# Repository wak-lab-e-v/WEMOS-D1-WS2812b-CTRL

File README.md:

# WEMOS D1 (ESP8266) LED Controller

Controller for WS2812B LED Strips / Panels / i.e. , optimized for the https://github.com/Aircoookie/WLED projekt

*Targets:*

- compact in a 3D printed case
- DC via hollow plug and 2A Step Down converter
- alternately over JST 3-pin (INPUT, 5V, data ignored)
- WEMOS D1 as controller
- diode protection for WEMOS D1 5V input
- Stabi-Elco in the 5V branch 
- Level Shift via 74HCT1G08GW
- Push button direct to controler (typically used as on/off via software)
- Infrarot support for IR-Remote
- PCB with Wemos-D1 und Step Down converter side-by-side

*LED Strip:*

- WS2812B-compatible RGB(W) led strip to GPIO2 / D2
- optional support for GPIO16 / D0 via solder bridge 
- level-shift via 74HCT1G08GW
- output via solder pads, JST 3-pin

*Push button:*

- a push button is connected to GPIO0 / D3

*Infrared:*

- recommended: TSOP38238
- Pinout: 2.5 V to 5.5 V, GND, Signal
- Signal to GPIO4 / D2 (can be changed in NpbWrapper.h)

*PCB:*

- D2 to Infrared solder pad
- D3 to button solder pad
- D4 to solder bridge/switch, level shifter, led signal solder pad
- D0 to solder bridge/switch, level shifter, led signal solder pad

*Wemos D1 Pinout:*

- A0	Analoger Eingang, max 3,3V	A0
- D0	IO	GPIO16
- D1	IO	GPIO5, SCL
- D2	IO	GPIO4, SDA
- D3	IO	GPIO0, 10k Pull-up
- D4	IO	GPIO2, 10k Pull-up, Onboard LED
- D5	IO  GPIO14, SCK	
- D6	IO	GPIO12, MISO
- D7	IO	GPIO13, MOSI
- D8	IO	GPIO15, 10k Pull-down, SS (Slave Select)
- GND
- 5V	(unprotected)
- 3V3	3,3V (from onboard step-down)

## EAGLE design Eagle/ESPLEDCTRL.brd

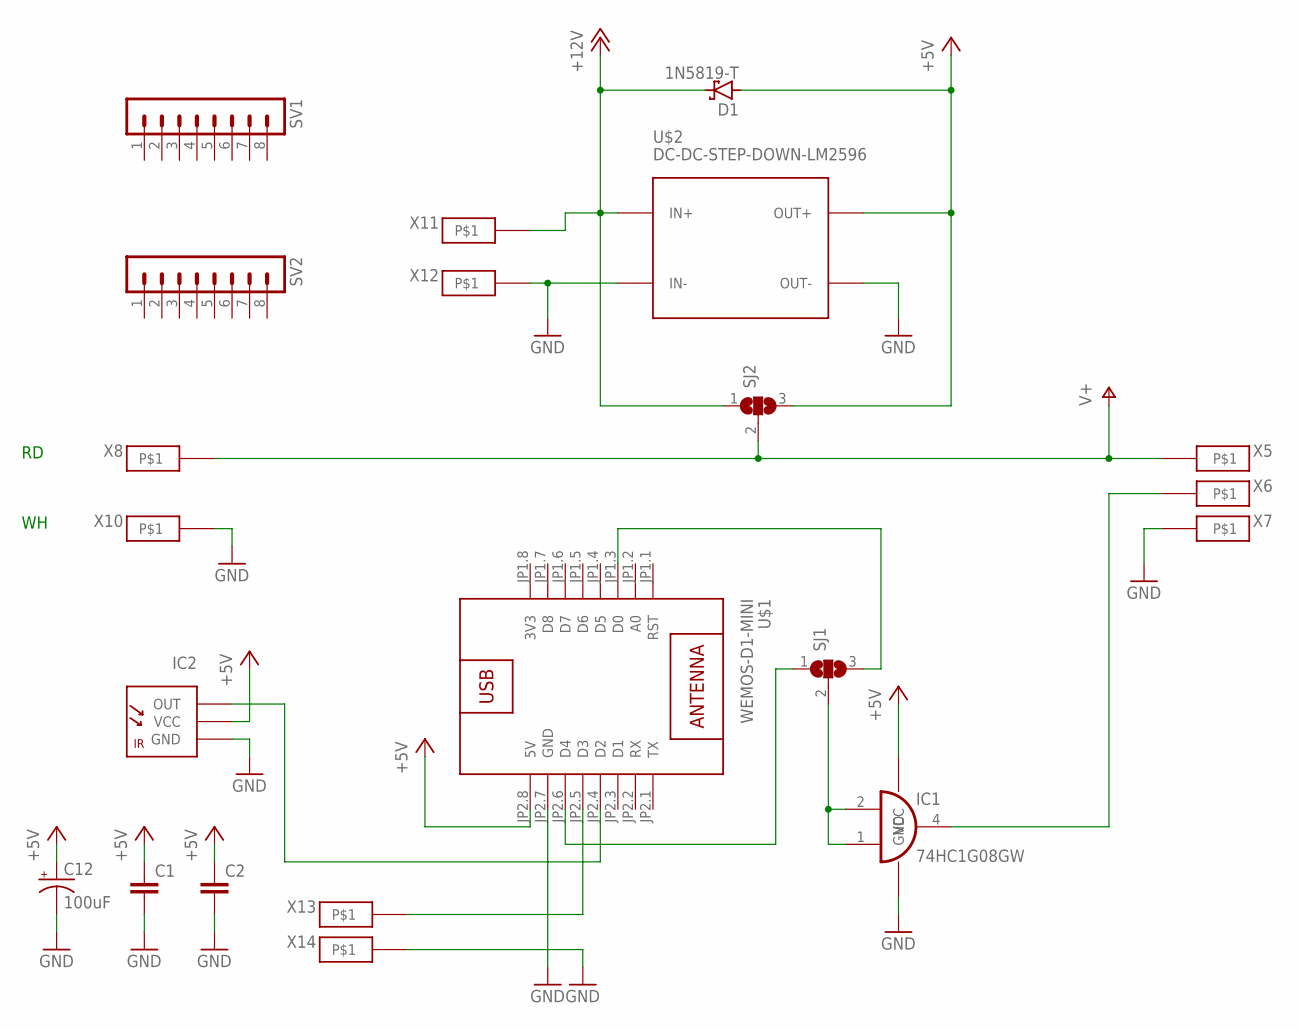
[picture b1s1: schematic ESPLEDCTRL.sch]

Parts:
C1, C2: C-EUC1206; C1206
C12: 100uF; PANASONIC_D
D1: 1N5819-T; DO41-7.6
IC1: 74HC1G08GW; SOT353
IC2: TSOP382; TSOP38
SJ1, SJ2: SJ2W; SJ_2
SV1, SV2: MA08-1
U$1: WEMOS-D1-MINI
U$2: DC-DC-STEP-DOWN-LM2596
X5, X6, X7, X8, X10, X11, X12, X13, X14: PAD2X4

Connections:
3V3: U$1.JP1.8 (3V3)
+5V: C1.1, C2.1, C12.+, D1.A, IC1.5 (VCC), IC2.3 (VCC), SJ2.3, U$1.JP2.8 (5V), U$2.OUT+
+12V: D1.C, SJ2.1, U$2.IN+, X11.P$1
GND: C1.2, C2.2, C12.-, IC1.3 (GND), IC2.2 (GND), U$1.JP2.7 (GND), U$2.IN-, U$2.OUT-, X7.P$1, X10.P$1, X12.P$1, X14.P$1
unnamed: U$1.JP2.5 (D3), X13.P$1
unnamed: IC2.1 (OUT), U$1.JP2.4 (D2)
unnamed: SJ1.1, U$1.JP2.6 (D4)
unnamed: IC1.1 (I1), IC1.2 (I0), SJ1.2
unnamed: SJ1.3, U$1.JP1.3 (D0)
unnamed: IC1.4 (O), X6.P$1
V+: SJ2.2, X5.P$1, X8.P$1

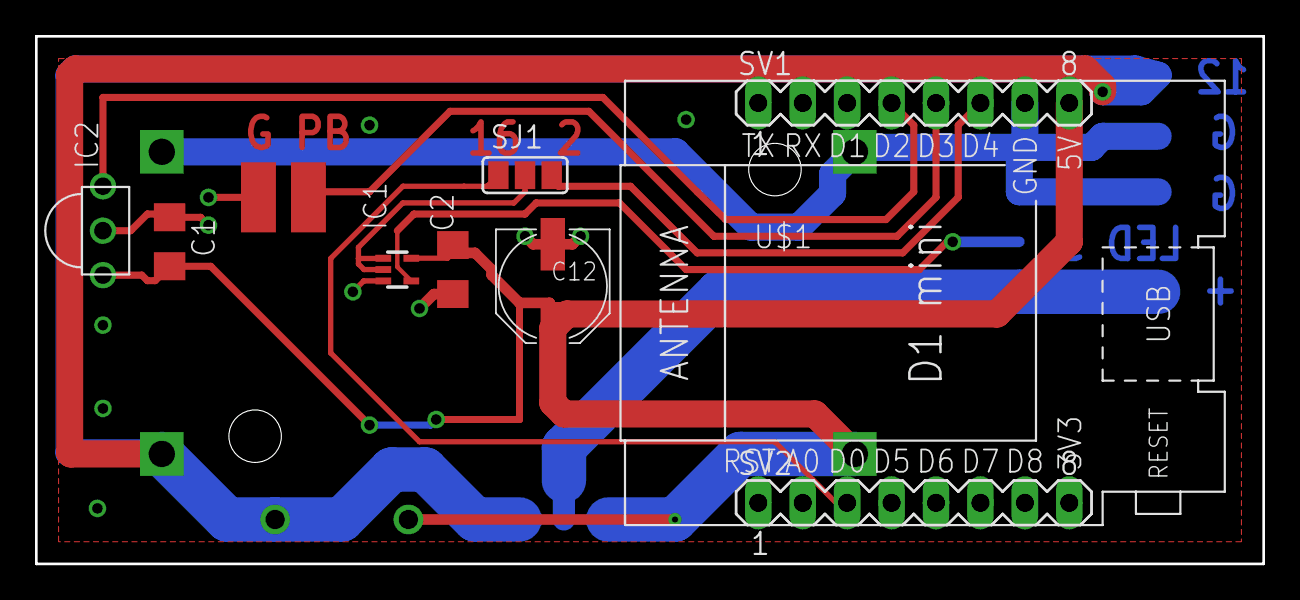
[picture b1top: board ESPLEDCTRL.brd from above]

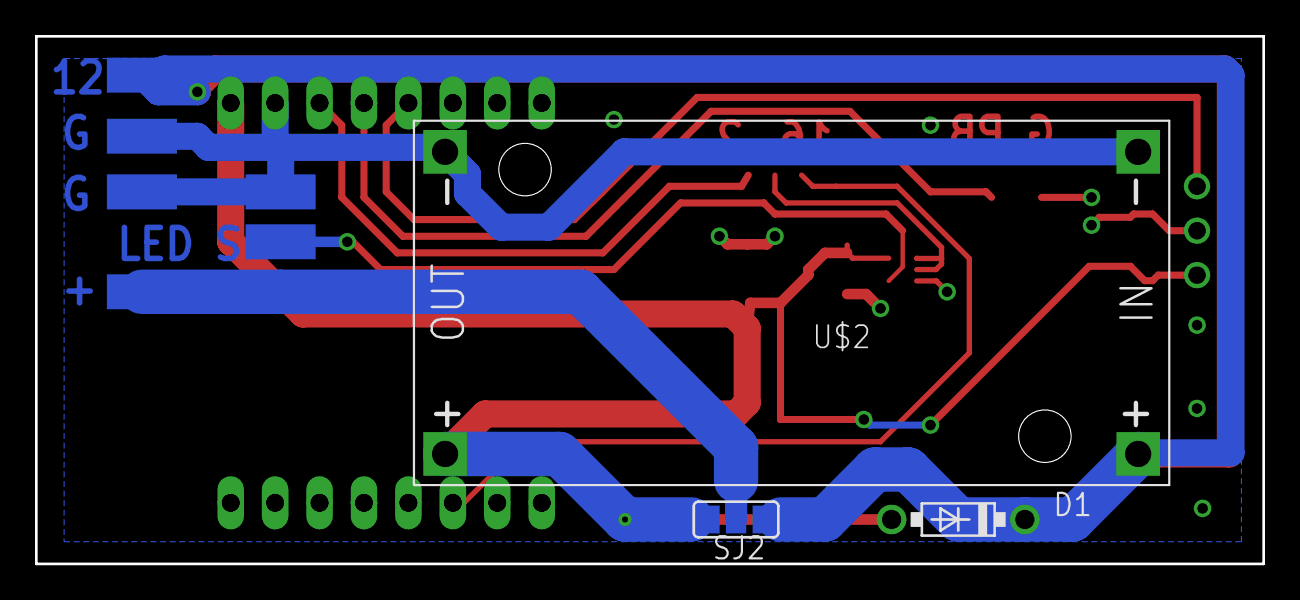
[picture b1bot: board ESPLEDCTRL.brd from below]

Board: 2 copper layers, 70.2 x 30.2 mm, 21 parts (10 on the bottom side), 10 nets.

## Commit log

2019-11-11 Initialversion
2019-11-11 Eine Diode
2019-11-11 Die Diode
2019-11-11 README.md
2019-11-13 some changes
2019-11-13 Fritzing Files added
2019-11-13 minimal changes
2020-05-03 Alte Version
2020-05-03 Umbau auf Version 2 beginnt
2020-06-21 Datasheet
2020-06-22 Leiterplatte Anordnung vorbereitet DCDC wandler ist 14mm hoch
2020-06-22 Schaltplan
2020-06-24 Board fertig gestellt
2022-06-07 Schaltplan.png aktualisiert, D1 eingefügt
2022-06-21 Umsortiert
2022-06-21 Bild
2023-04-06 Pacages
2023-04-07 LM2596

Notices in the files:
parts and their libraries:
diy-modules: Released under the Creative Commons Attribution 4.0 International License: http://creativecommons.org/licenses/by/4.0
